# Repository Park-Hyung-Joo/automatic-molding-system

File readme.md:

--------------------------------------------
# Plastic Injection Molding Control System

## Abstract

This work was developed by the startup 'The Fourth Space', where senior Kim Seong-jun from the 17th generation of Barami is affiliated, as an outsourcing project for Barami's plastic injection molding machine control system.

The system is mainly divided into a heating bed (heater) that melts the plastic, a temperature sensor, and a solenoid valve that applies pressure to the melted plastic. Both the heater and the valve operate on 220VAC alternating current.

To control the 220VAC AC heater, a triac, a bidirectional switching device, was used. To control multiple triacs, each control signal is input to a 3-state buffer using a shift resistor, and the control signal is generated at the appropriate timing through a zero-detection circuit to turn the buffer on/off. This method allows for controlling the power of the AC heater. Additionally, the temperature of the AC heater is measured using a K-type temperature sensor, and by comparing it with the target temperature, the AC heater can be controlled within a range of 10 degrees of error through ON/OFF control. The solenoid valve also operates on 220VAC, so it is controlled in the same way using a triac.

--------------------------------------------------

## 220VAC Heater Control

### Triac

A triac is a bidirectional switching device for high voltage and high current. When a pulse signal is given to the Gate, it shorts between A1 and A2 as long as the voltage value is above a certain level, and it disconnects again when the voltage drops below a threshold. The direction doesn't matter. In other words, by providing a pulse when the instantaneous voltage of the AC is 0, AC current can flow through the triac. This can be used to control the current flowing to the heater and valve.

## Triac control system

### Optocoupler Circuit

When pulses are provided to tr1~tr6 at the appropriate timing, AC current flows to the heaters connected to J3, J4, and J5. When the pulse supply is stopped, the current is cut off from the moment the AC instantaneous voltage becomes 0. The MOC3021(U1U6) device is an optocoupler, which separates the high current, high voltage AC circuit from the low voltage, low current DC circuit.

### Pulse Generator

The circuit that generates the pulse produces a pulse at J3 the moment the AC voltage becomes 0. The detailed principle is as follows:

220VAC is rectified through bridge diodes and, through a resistor, provides the Photocoupler 4N35 with a rectified signal that has the same phase as 220VAC but at a lower voltage. When voltage is applied to the primary side of the 4N35, the secondary side's bjt operates, making the zero detection signal become 0. When the primary side voltage is 0, the bjt does not operate, and the zero detection voltage becomes VDC. Therefore, a pulse is generated the moment the voltage of 220VAC becomes 0.

This pulse is input into the 3-state buffer circuit.

### Tri-state Buffers

The tri-state buffer (buffer hereafter) circuit is divided into pulseIn, signal input, and pulseOut. When 0 is input to the signal input, the buffer passes the pulse, and when 1 is input, the pulse is blocked in the buffer. PulseOut is connected to tr1~tr6 of the above optocoupler circuit (there are a total of 3 optocoupler circuit boards). The triac is controlled by determining the signal value given to the buffer from the Arduino.

### Shift Registers

Directly inputting signals from the Arduino is unstable due to reasons like the insufficient number of Arduino pins and unstable signal current. Therefore, a method was chosen to store pre-determined signals in the shift register and connect the shift register output to the buffer signal end.

--------------------------------------------

## Temperature Measuring

To determine the current supplied to the heater, the temperature of the heating blocks must be measured. The temperature measurement circuit is composed of multiple temperature sensors and a decoder circuit to control them

### Temperature Sensers

The advantage of the K-type temperature sensor is its wide usable temperature range. It's suitable for systems that need to operate at high temperatures, which is why it was used in this project.

### Temperature Senser Connection Bus

The temperature sensor communicates its measurements to the Arduino via SPI communication. SCK is the clock, SO is the data, and CS is the pin that determines the communication blockage.

### Decoders

Since the Arduino can access only one temperature sensor at a time, only the selected temperature sensor should be connected to the Arduino, and the rest should be temporarily disconnected. The CS pin of the temperature sensor serves this function, and the values to be input into the CS pins are output through the decoder. The Arduino selects the temperature sensor to connect by inputting binary numbers to the decoder.

---------------------------------------------------------

## Solenoid Valve
<video src="./assets/img/valve.mp4" width="720px"></video>

A solenoid valve is applied to press the melted plastic. The control method is the same as the heater, using a triac. Since the same type of circuit is used, a detailed circuit description is omitted.

--------------------------------------------------------

## Raspberry Pi

While controlling the system with Arduino is sufficient, the client requested remote control functionality through a web application, so the Arduino was connected to the web via a Raspberry Pi.

--------------------------------------------------------

## Assembled Borads

This is how the circuit board looks when connected to the machine.

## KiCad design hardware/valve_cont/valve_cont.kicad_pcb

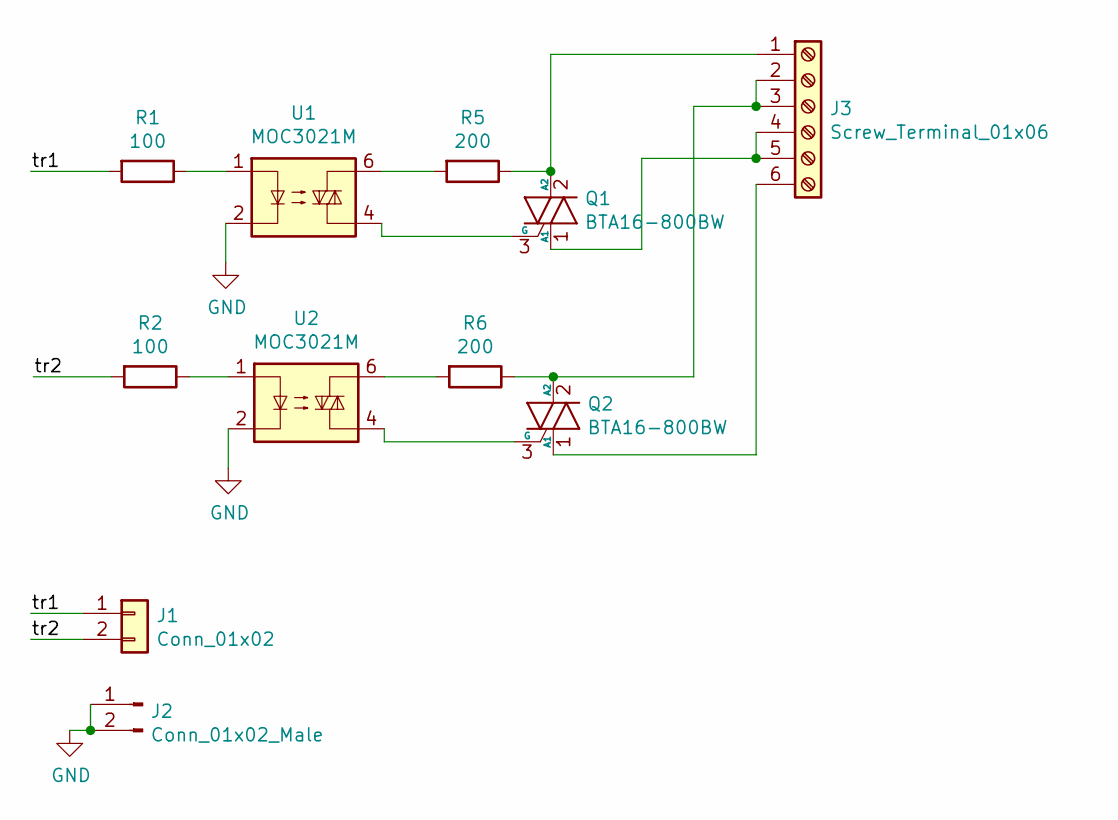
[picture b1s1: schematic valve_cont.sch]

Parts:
J1: Conn_01x02; Molex_SPOX_5267-02A_1x02_P2.50mm_Vertical
J2: Conn_01x02_Male; Molex_SPOX_5267-02A_1x02_P2.50mm_Vertical
J3: Screw_Terminal_01x06; BR_762K_6pin
Q1, Q2: BTA16-800BW; TO-220-3_Vertical
R1, R2: 100; R_Axial_DIN0207_L6.3mm_D2.5mm_P2.54mm_Vertical
R5, R6: 200; R_Axial_DIN0207_L6.3mm_D2.5mm_P2.54mm_Vertical
U1, U2: MOC3021M; DIP-6_W7.62mm_Socket

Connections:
/tr1: J1.1, R1.2
/tr2: J1.2, R2.2
GND: J2.1, J2.2, U1.2, U2.2
unnamed: J3.1, Q1.2 (A2), R5.1
unnamed: J3.2, J3.3, Q2.2 (A2), R6.1
unnamed: J3.4, J3.5, Q1.1 (A1)
unnamed: J3.6, Q2.1 (A1)
unnamed: Q1.3 (G), U1.4
unnamed: Q2.3 (G), U2.4
unnamed: R1.1, U1.1
unnamed: R2.1, U2.1
unnamed: R5.2, U1.6
unnamed: R6.2, U2.6

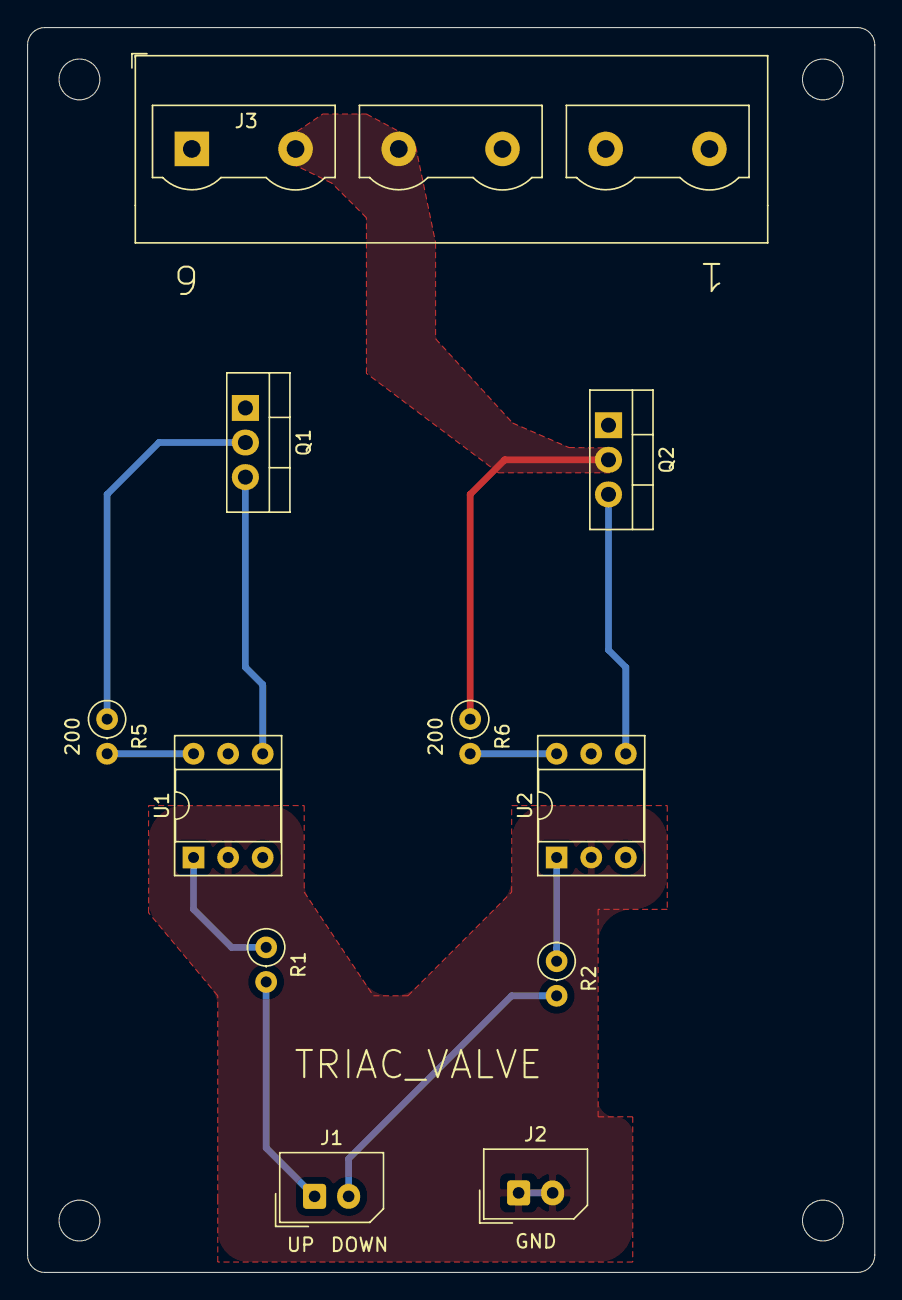
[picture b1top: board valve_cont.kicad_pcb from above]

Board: 2 copper layers, 62.2 x 91.4 mm, 11 parts (0 on the bottom side), 13 nets.

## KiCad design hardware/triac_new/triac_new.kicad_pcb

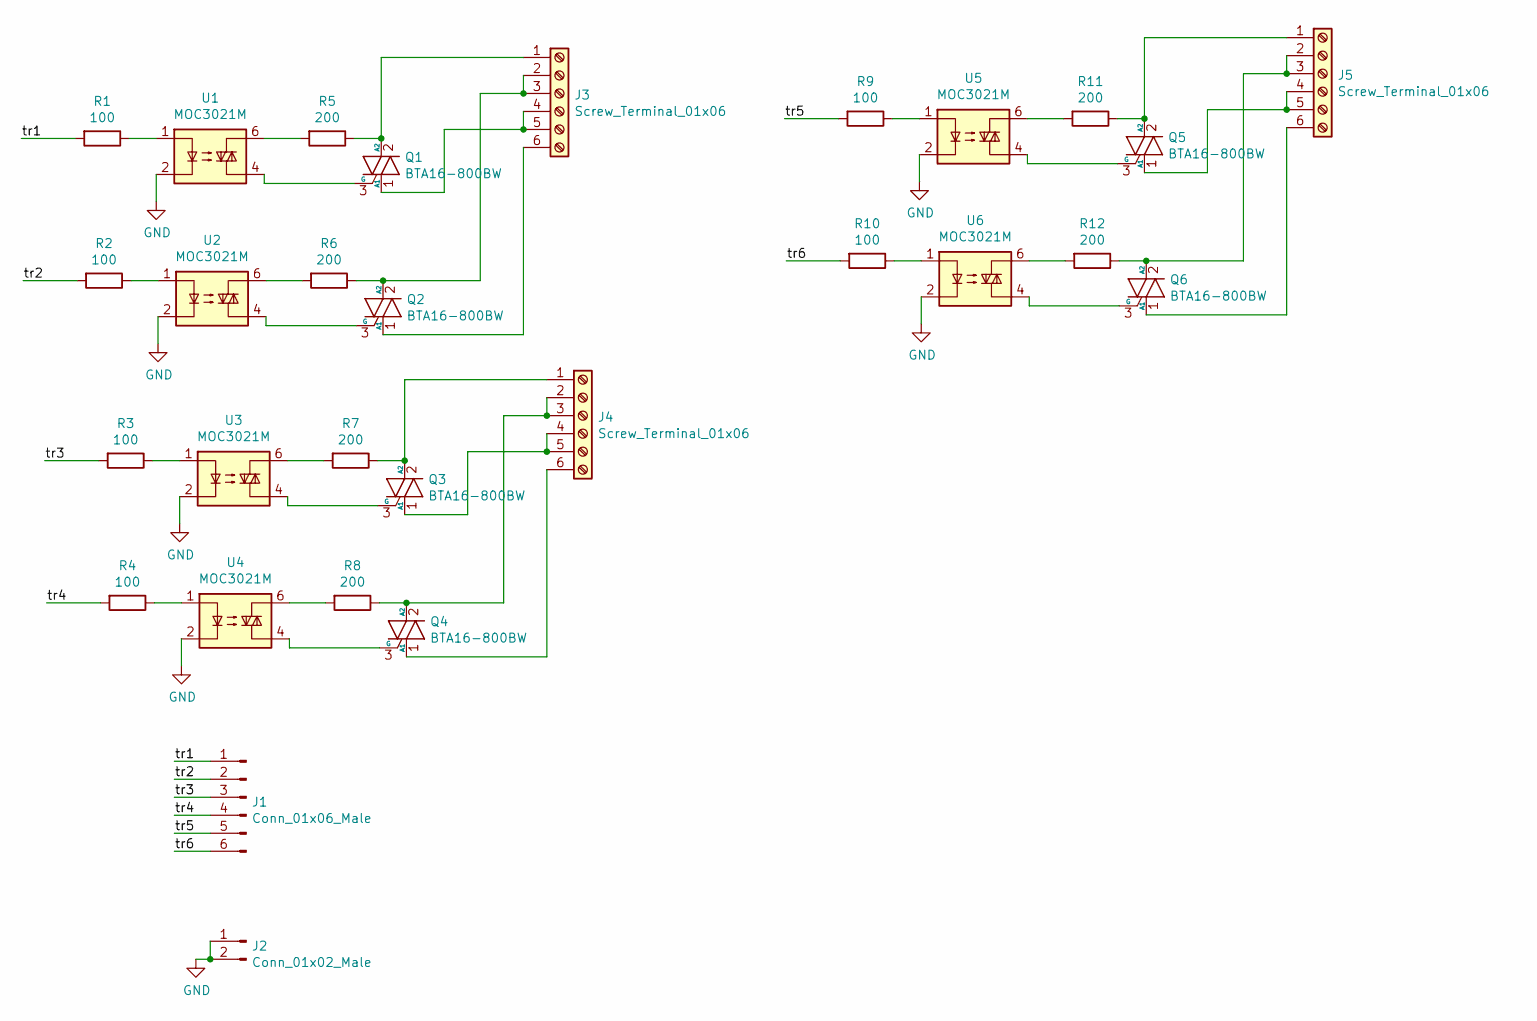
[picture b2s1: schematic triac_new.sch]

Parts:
J1: Conn_01x06_Male; Molex_SPOX_5267-06A_1x06_P2.50mm_Vertical
J2: Conn_01x02_Male; Molex_SPOX_5267-02A_1x02_P2.50mm_Vertical
J3, J4, J5: Screw_Terminal_01x06; BR_762K_6pin
Q1, Q2, Q3, Q4, Q5, Q6: BTA16-800BW; TO-220-3_Vertical
R1, R2, R3, R4, R9, R10: 100; R_Axial_DIN0207_L6.3mm_D2.5mm_P2.54mm_Vertical
R5, R6, R7, R8, R11, R12: 200; R_Axial_DIN0207_L6.3mm_D2.5mm_P2.54mm_Vertical
U1, U2, U3, U4, U5, U6: MOC3021M; DIP-6_W7.62mm_Socket

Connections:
/tr1: J1.1, R1.2
/tr2: J1.2, R2.2
/tr3: J1.3, R3.2
/tr4: J1.4, R4.2
/tr5: J1.5, R9.2
/tr6: J1.6, R10.2
GND: J2.1, J2.2, U1.2, U2.2, U3.2, U4.2, U5.2, U6.2
unnamed: J3.1, Q1.2 (A2), R5.1
unnamed: J3.2, J3.3, Q2.2 (A2), R6.1
unnamed: J3.4, J3.5, Q1.1 (A1)
unnamed: J3.6, Q2.1 (A1)
unnamed: J4.1, Q3.2 (A2), R7.1
unnamed: J4.2, J4.3, Q4.2 (A2), R8.1
unnamed: J4.4, J4.5, Q3.1 (A1)
unnamed: J4.6, Q4.1 (A1)
unnamed: J5.1, Q5.2 (A2), R11.1
unnamed: J5.2, J5.3, Q6.2 (A2), R12.1
unnamed: J5.4, J5.5, Q5.1 (A1)
unnamed: J5.6, Q6.1 (A1)
unnamed: Q1.3 (G), U1.4
unnamed: Q2.3 (G), U2.4
unnamed: Q3.3 (G), U3.4
unnamed: Q4.3 (G), U4.4
unnamed: Q5.3 (G), U5.4
unnamed: Q6.3 (G), U6.4
unnamed: R1.1, U1.1
unnamed: R2.1, U2.1
unnamed: R3.1, U3.1
unnamed: R4.1, U4.1
unnamed: R5.2, U1.6
unnamed: R6.2, U2.6
unnamed: R7.2, U3.6
unnamed: R8.2, U4.6
unnamed: R9.1, U5.1
unnamed: R10.1, U6.1
unnamed: R11.2, U5.6
unnamed: R12.2, U6.6

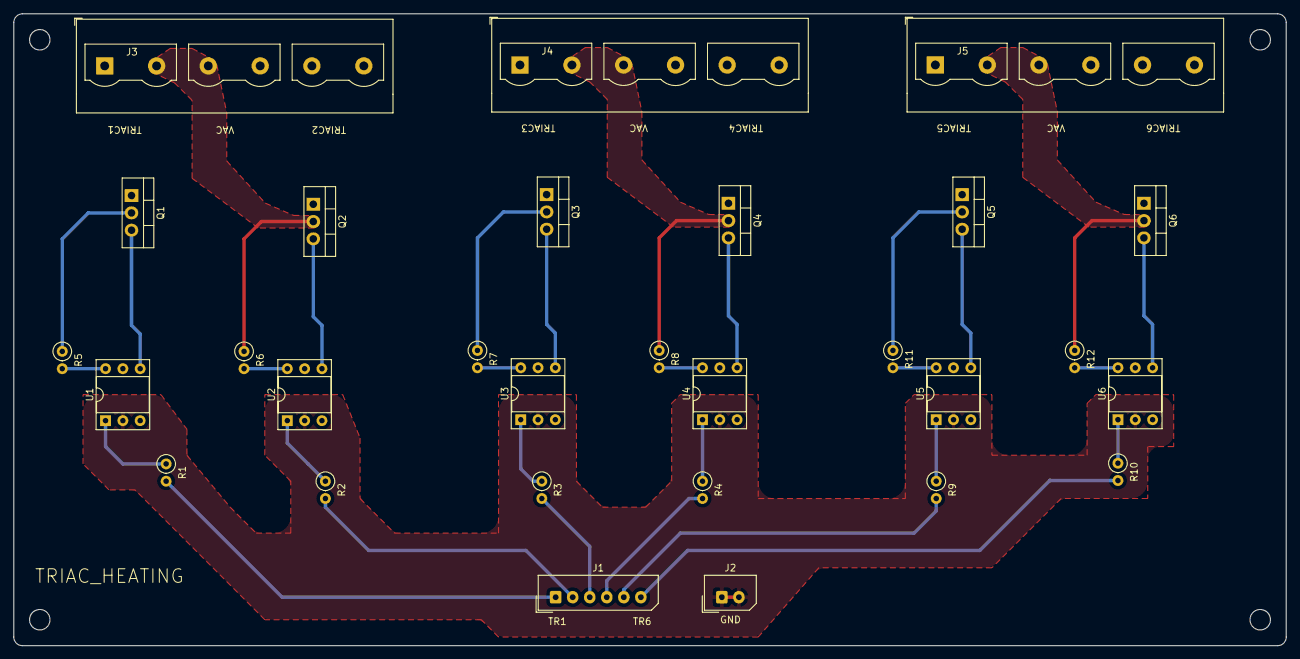
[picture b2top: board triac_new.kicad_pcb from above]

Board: 2 copper layers, 186.7 x 92.7 mm, 29 parts (0 on the bottom side), 37 nets.

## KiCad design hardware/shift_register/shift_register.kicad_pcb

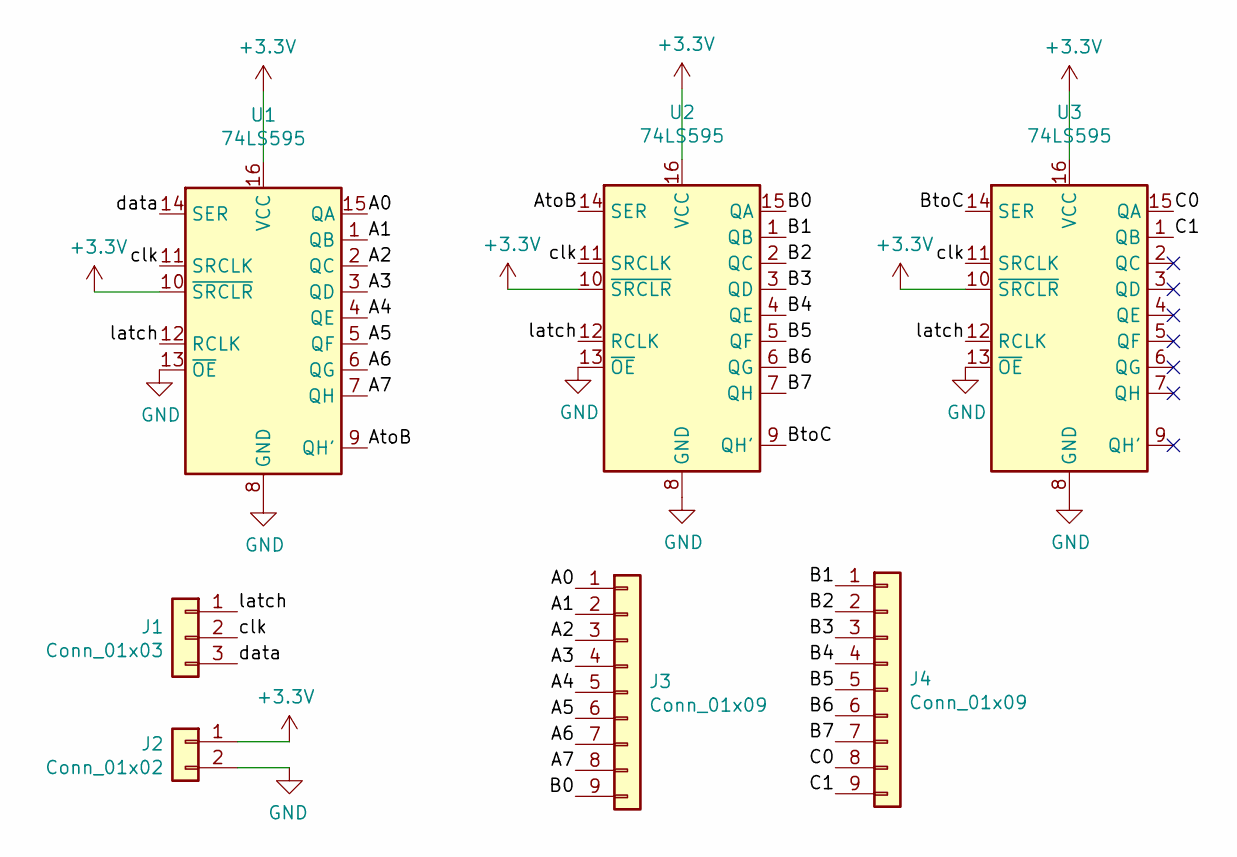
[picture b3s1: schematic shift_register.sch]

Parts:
J1: Conn_01x03; Molex_SPOX_5267-03A_1x03_P2.50mm_Vertical
J2: Conn_01x02; Molex_SPOX_5267-02A_1x02_P2.50mm_Vertical
J3, J4: Conn_01x09; Molex_SPOX_5267-09A_1x09_P2.50mm_Vertical
U1, U2, U3: 74LS595; DIP-16_W7.62mm_Socket

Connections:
+3V3: J2.1, U1.10 (~SRCLR), U1.16 (VCC), U2.10 (~SRCLR), U2.16 (VCC), U3.10 (~SRCLR), U3.16 (VCC)
/A0: J3.1, U1.15 (QA)
/A1: J3.2, U1.1 (QB)
/A2: J3.3, U1.2 (QC)
/A3: J3.4, U1.3 (QD)
/A4: J3.5, U1.4 (QE)
/A5: J3.6, U1.5 (QF)
/A6: J3.7, U1.6 (QG)
/A7: J3.8, U1.7 (QH)
/AtoB: U1.9 (QH'), U2.14 (SER)
/B0: J3.9, U2.15 (QA)
/B1: J4.1, U2.1 (QB)
/B2: J4.2, U2.2 (QC)
/B3: J4.3, U2.3 (QD)
/B4: J4.4, U2.4 (QE)
/B5: J4.5, U2.5 (QF)
/B6: J4.6, U2.6 (QG)
/B7: J4.7, U2.7 (QH)
/BtoC: U2.9 (QH'), U3.14 (SER)
/C0: J4.8, U3.15 (QA)
/C1: J4.9, U3.1 (QB)
/clk: J1.2, U1.11 (SRCLK), U2.11 (SRCLK), U3.11 (SRCLK)
/data: J1.3, U1.14 (SER)
/latch: J1.1, U1.12 (RCLK), U2.12 (RCLK), U3.12 (RCLK)
GND: J2.2, U1.8 (GND), U1.13 (~OE), U2.8 (GND), U2.13 (~OE), U3.8 (GND), U3.13 (~OE)

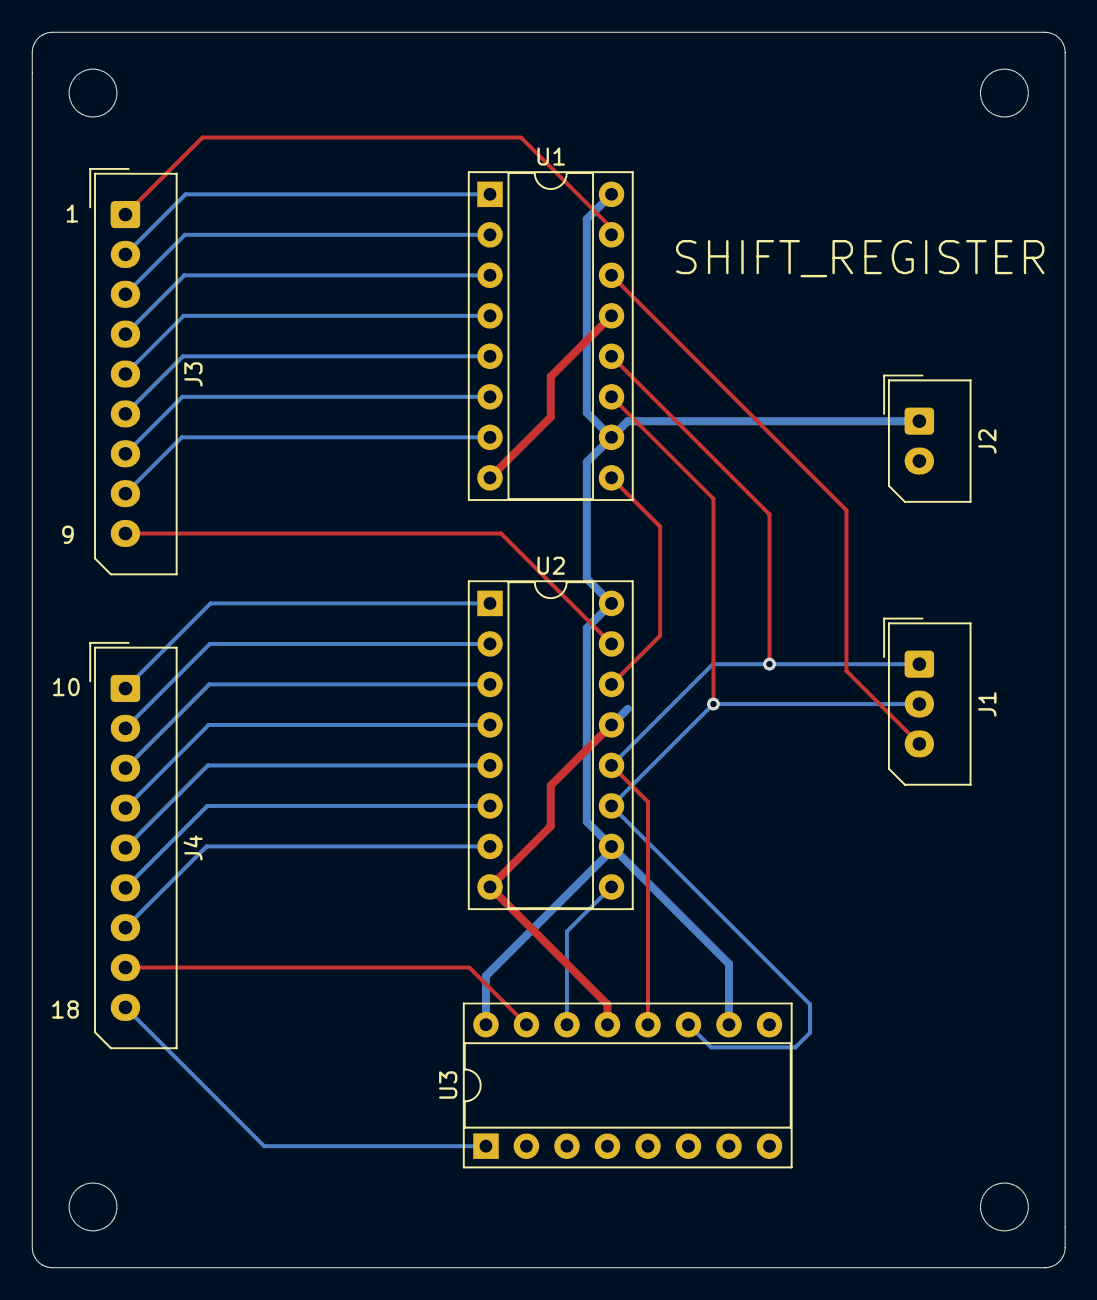
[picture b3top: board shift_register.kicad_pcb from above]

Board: 2 copper layers, 64.8 x 77.5 mm, 7 parts (0 on the bottom side), 25 nets.

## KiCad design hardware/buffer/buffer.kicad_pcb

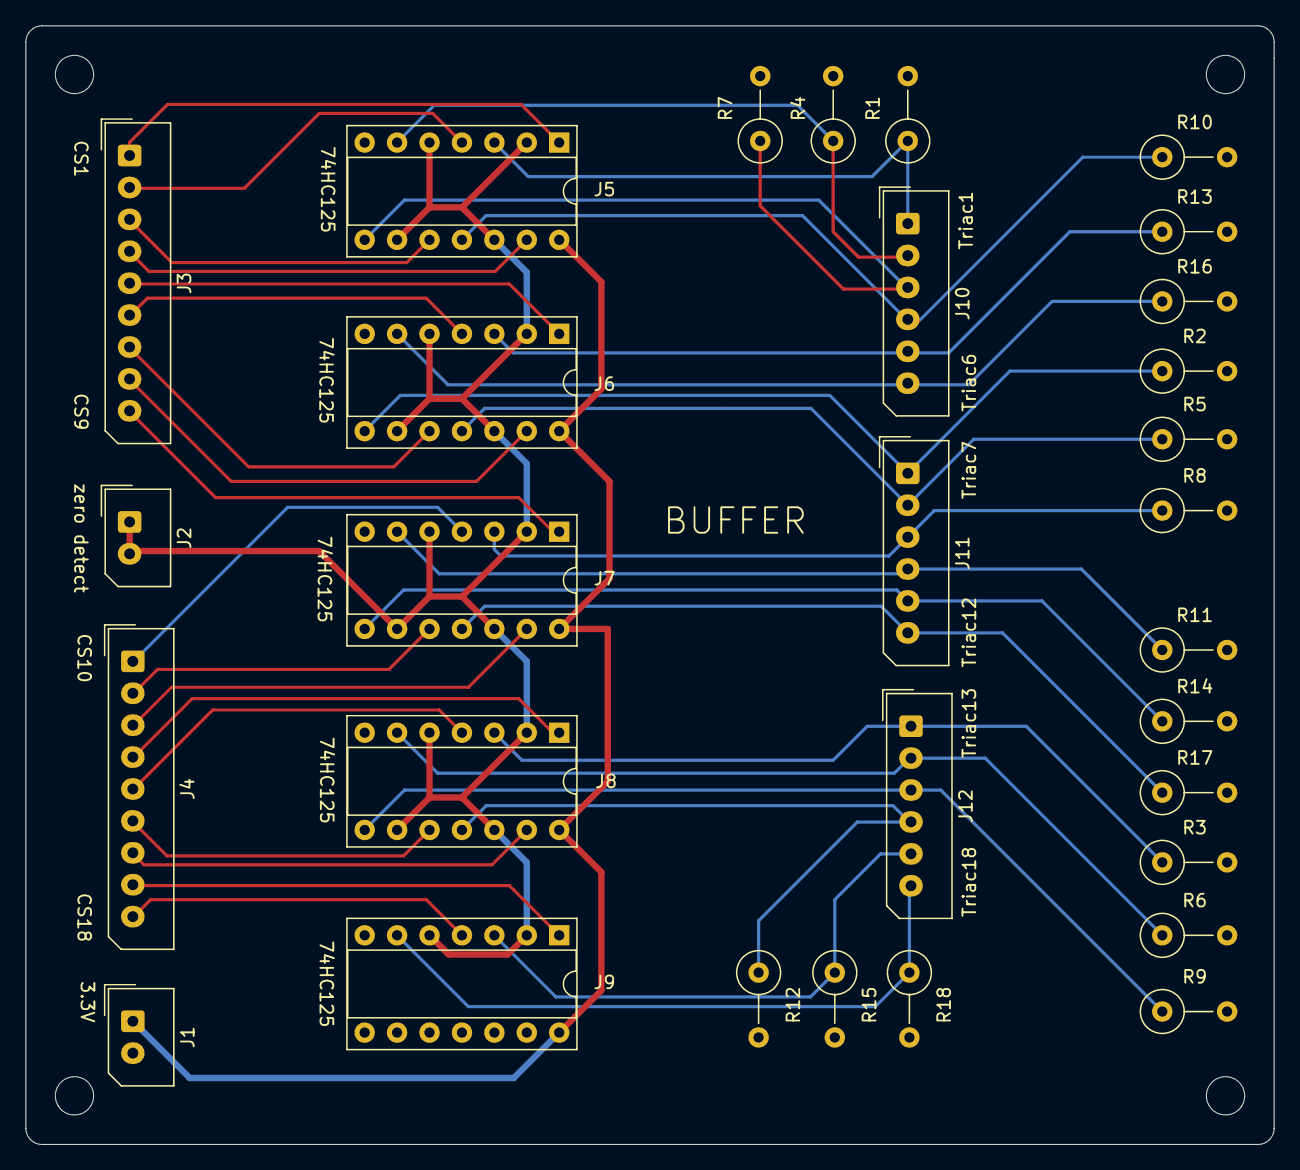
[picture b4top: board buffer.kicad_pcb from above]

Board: 2 copper layers, 97.8 x 87.6 mm, 30 parts (0 on the bottom side), 39 nets.

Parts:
J1, J2: Conn_01x02; Molex_SPOX_5267-02A_1x02_P2.50mm_Vertical
J3, J4: Conn_01x09; Molex_SPOX_5267-09A_1x09_P2.50mm_Vertical
J5, J6, J7, J8, J9: Conn_02x07_Counter_Clockwise; DIP-14_W7.62mm_Socket
J10, J11, J12: Conn_01x06; Molex_SPOX_5267-06A_1x06_P2.50mm_Vertical
R1, R2, R3, R4, R5, R6, R7, R8, R9, R10, R11, R12, R13, R14, R15, R16, R17, R18: R; R_Axial_DIN0309_L9.0mm_D3.2mm_P5.08mm_Vertical

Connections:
+3V3: J1.1, J5.14, J6.14, J7.14, J8.14, J9.14
/C1: J3.1, J5.1
/C2: J3.2, J5.4
/C3: J3.3, J5.10
/C4: J3.4, J5.13
/C5: J3.5, J6.1
/C6: J3.6, J6.4
/C7: J3.7, J6.10
/C8: J3.8, J6.13
/C9: J3.9, J7.1
/C10: J4.1, J7.4
/C11: J4.2, J7.10
/C12: J4.3, J7.13
/C13: J4.4, J8.1
/C14: J4.5, J8.4
/C15: J4.6, J8.10
/C16: J4.7, J8.13
/C17: J4.8, J9.1
/C18: J4.9, J9.4
/Tri1: J5.3, J10.1, R1.1
/Tri2: J5.6, J10.2, R4.1
/Tri3: J5.8, J10.3, R7.1
/Tri4: J5.11, J10.4, R10.1
/Tri5: J6.3, J10.5, R13.1
/Tri6: J6.6, J10.6, R16.1
/Tri7: J6.8, J11.1, R2.1
/Tri8: J6.11, J11.2, R5.1
/Tri9: J7.3, J11.3, R8.1
/Tri10: J7.6, J11.4, R11.1
/Tri11: J7.8, J11.5, R14.1
/Tri12: J7.11, J11.6, R17.1
/Tri13: J8.3, J12.1, R3.1
/Tri14: J8.6, J12.2, R6.1
/Tri15: J8.8, J12.3, R9.1
/Tri16: J8.11, J12.4, R12.1
/Tri17: J9.3, J12.5, R15.1
/Tri18: J9.6, J12.6, R18.1
/pulse: J2.1, J2.2, J5.2, J5.5, J5.9, J5.12, J6.2, J6.5, J6.9, J6.12, J7.2, J7.5, J7.9, J7.12, J8.2, J8.5, J8.9, J8.12, J9.2, J9.5
GND: J1.2, J5.7, J6.7, J7.7, J8.7, J9.7, R1.2, R2.2, R3.2, R4.2, R5.2, R6.2, R7.2, R8.2, R9.2, R10.2, R11.2, R12.2, R13.2, R14.2, R15.2, R16.2, R17.2, R18.2

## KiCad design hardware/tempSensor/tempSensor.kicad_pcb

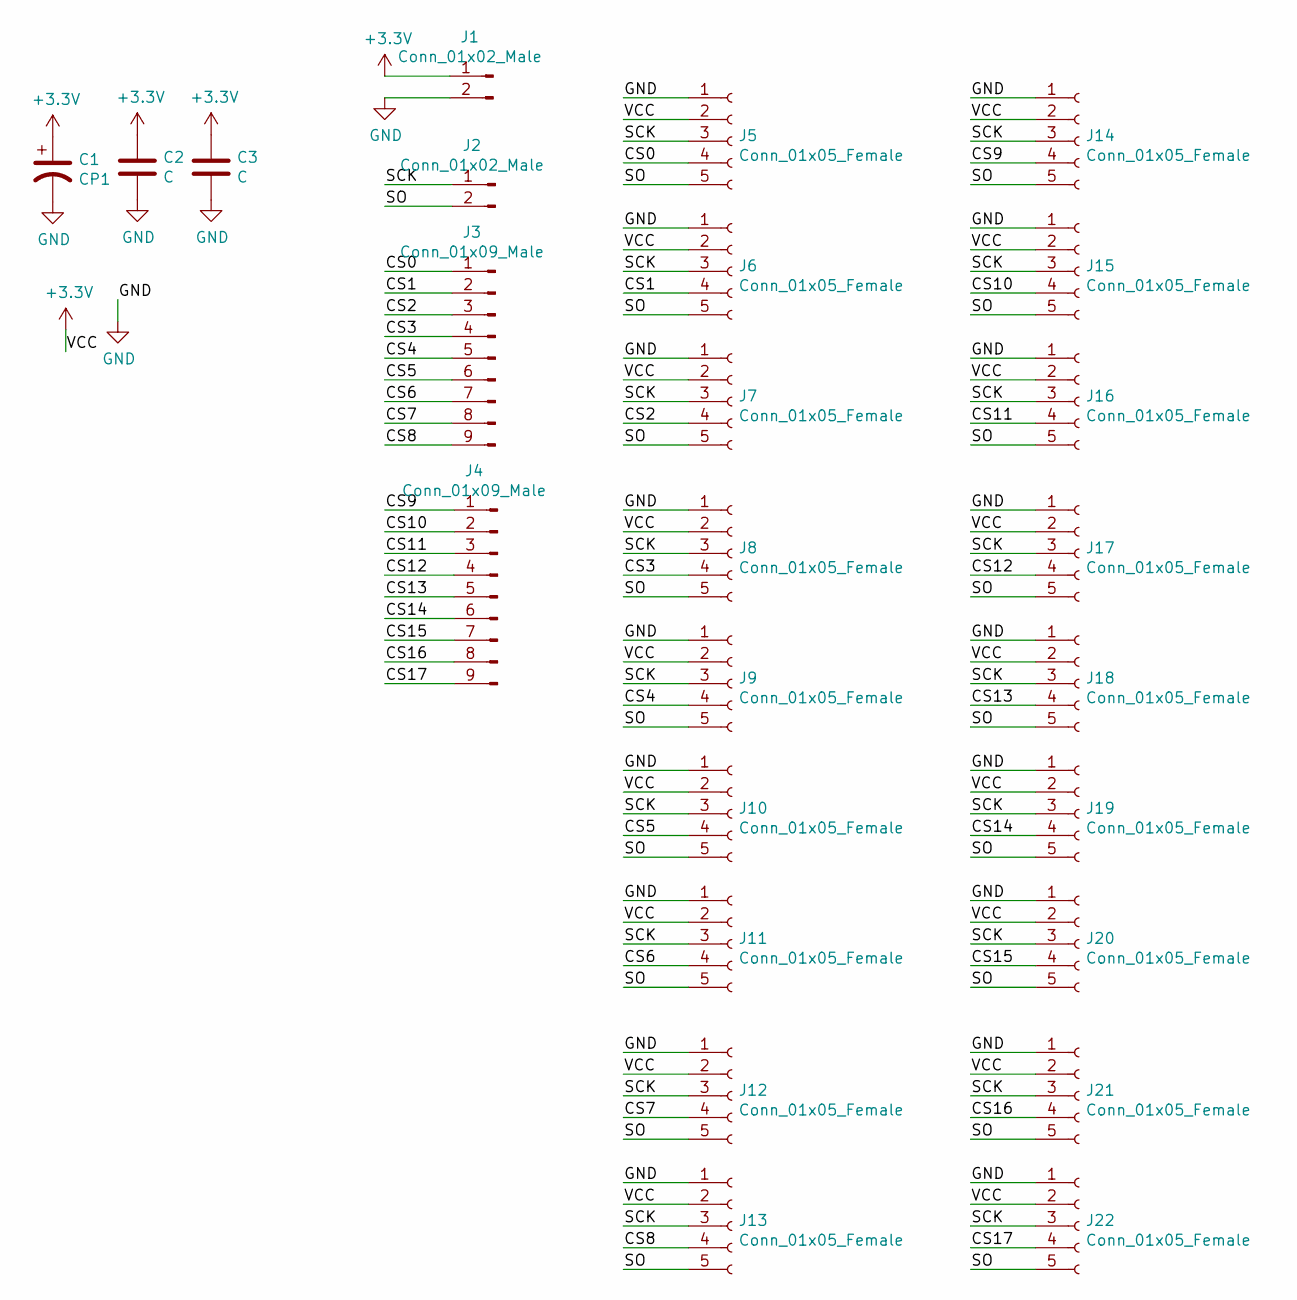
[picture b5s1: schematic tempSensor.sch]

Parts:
C1: CP1; CP_Radial_D8.0mm_P5.00mm
C2, C3: C; C_Axial_L3.8mm_D2.6mm_P7.50mm_Horizontal
J1, J2: Conn_01x02_Male; Molex_SPOX_5267-02A_1x02_P2.50mm_Vertical
J3, J4: Conn_01x09_Male; Molex_SPOX_5267-09A_1x09_P2.50mm_Vertical
J5, J6, J7, J8, J9, J10, J11, J12, J13, J14, J15, J16, J17, J18, J19, J20, J21, J22: Conn_01x05_Female; PinSocket_1x05_P2.54mm_Vertical

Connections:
+3V3: C1.1, C2.1, C3.1, J1.1, J5.2, J6.2, J7.2, J8.2, J9.2, J10.2, J11.2, J12.2, J13.2, J14.2, J15.2, J16.2, J17.2, J18.2, J19.2, J20.2, J21.2, J22.2
/CS0: J3.1, J5.4
/CS1: J3.2, J6.4
/CS2: J3.3, J7.4
/CS3: J3.4, J8.4
/CS4: J3.5, J9.4
/CS5: J3.6, J10.4
/CS6: J3.7, J11.4
/CS7: J3.8, J12.4
/CS8: J3.9, J13.4
/CS9: J4.1, J14.4
/CS10: J4.2, J15.4
/CS11: J4.3, J16.4
/CS12: J4.4, J17.4
/CS13: J4.5, J18.4
/CS14: J4.6, J19.4
/CS15: J4.7, J20.4
/CS16: J4.8, J21.4
/CS17: J4.9, J22.4
/SCK: J2.1, J5.3, J6.3, J7.3, J8.3, J9.3, J10.3, J11.3, J12.3, J13.3, J14.3, J15.3, J16.3, J17.3, J18.3, J19.3, J20.3, J21.3, J22.3
/SO: J2.2, J5.5, J6.5, J7.5, J8.5, J9.5, J10.5, J11.5, J12.5, J13.5, J14.5, J15.5, J16.5, J17.5, J18.5, J19.5, J20.5, J21.5, J22.5
GND: C1.2, C2.2, C3.2, J1.2, J5.1, J6.1, J7.1, J8.1, J9.1, J10.1, J11.1, J12.1, J13.1, J14.1, J15.1, J16.1, J17.1, J18.1, J19.1, J20.1, J21.1, J22.1

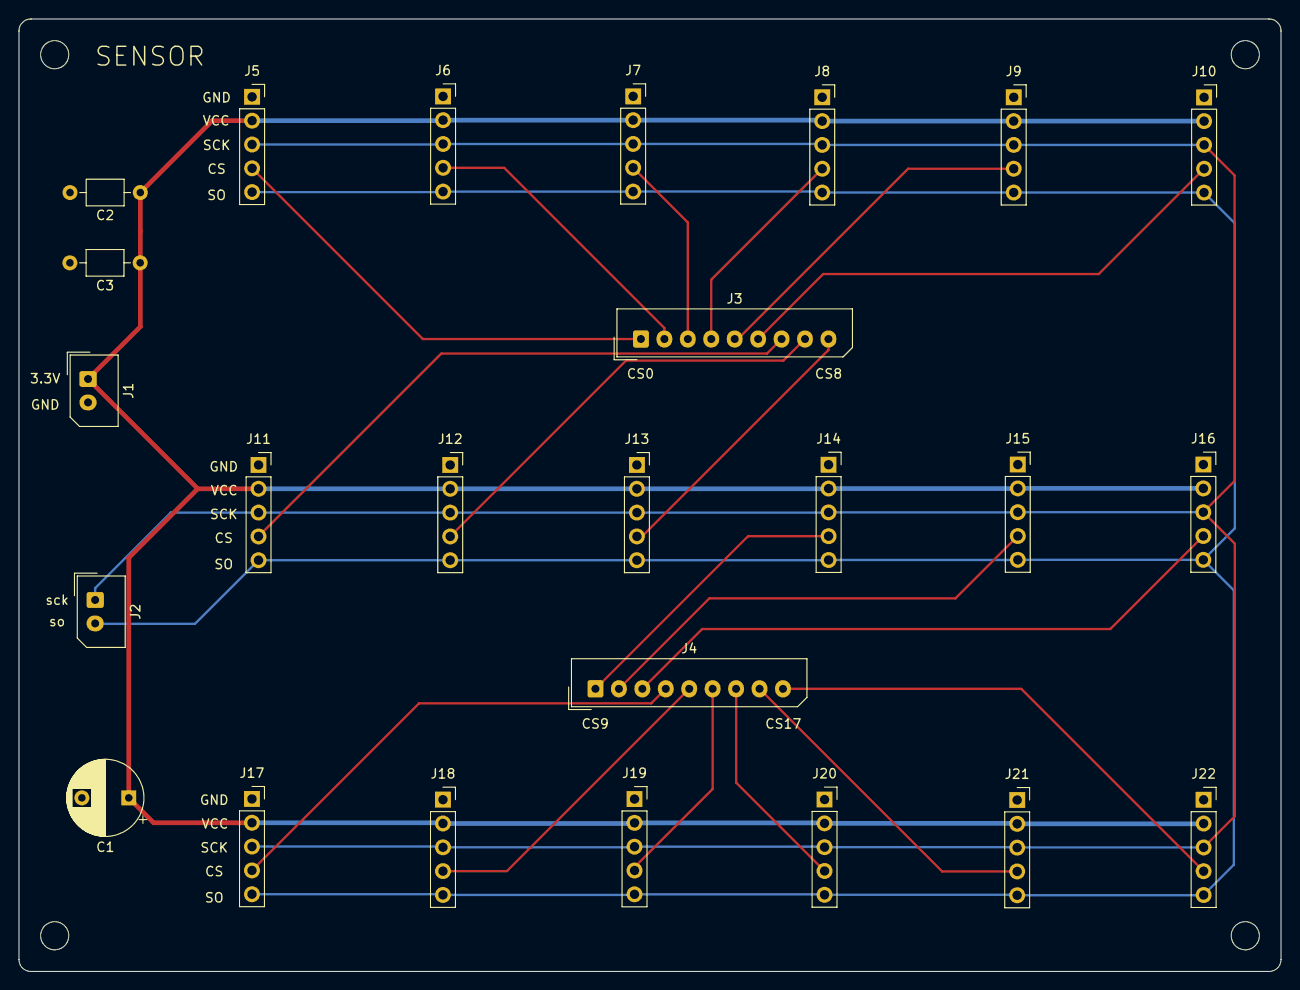
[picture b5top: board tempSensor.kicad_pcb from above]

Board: 2 copper layers, 134.6 x 101.6 mm, 25 parts (0 on the bottom side), 22 nets.

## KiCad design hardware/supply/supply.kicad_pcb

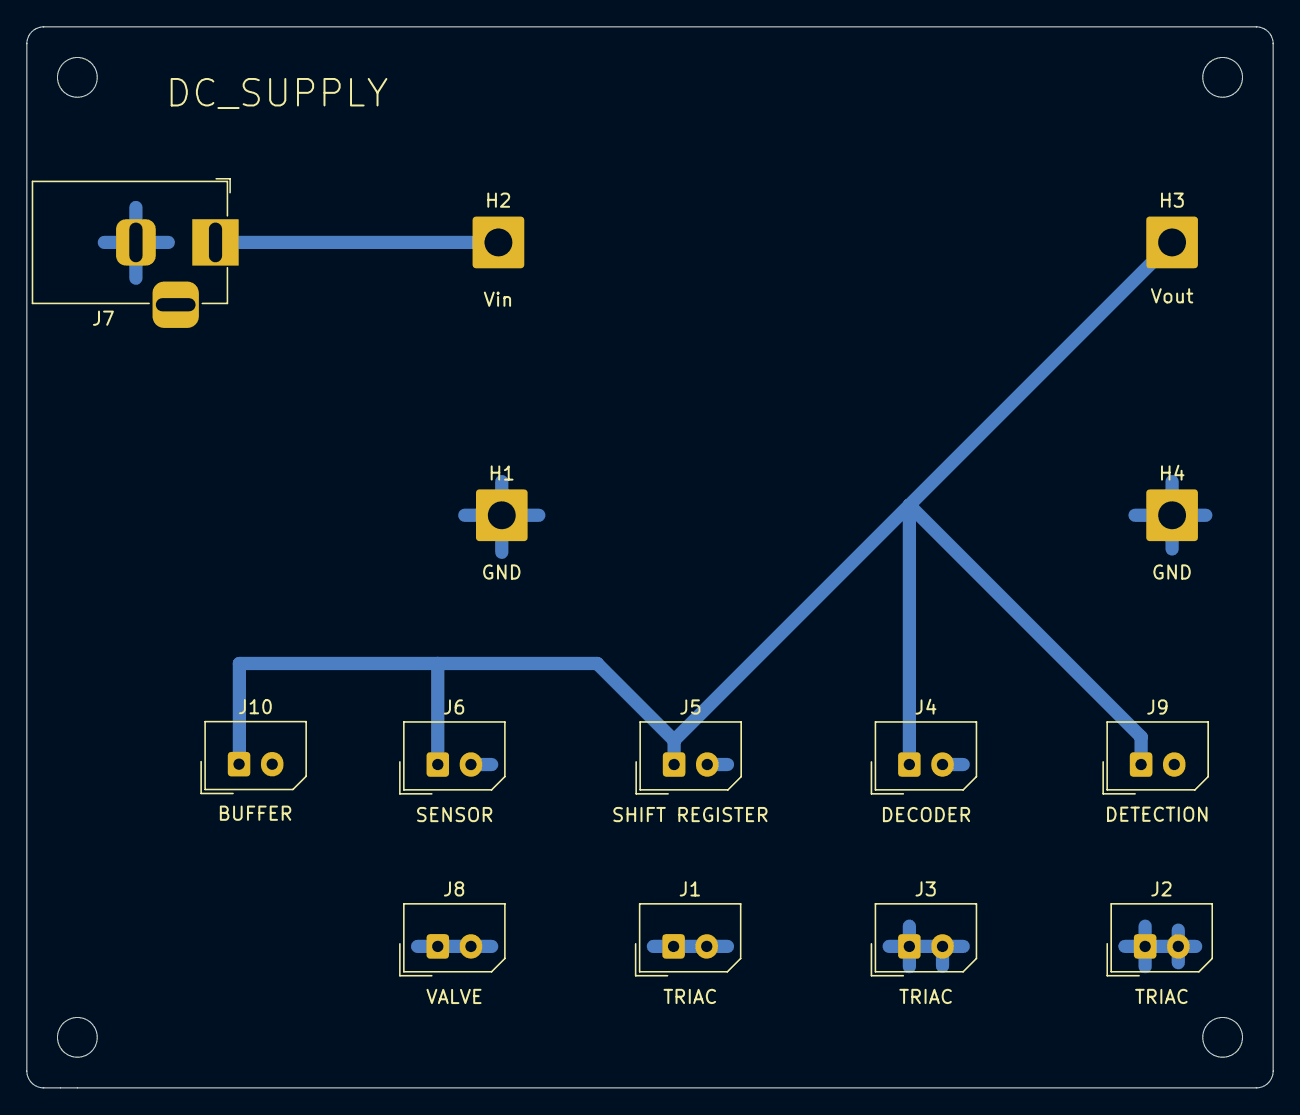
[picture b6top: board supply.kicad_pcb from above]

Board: 2 copper layers, 94.0 x 80.0 mm, 14 parts (0 on the bottom side), 3 nets.

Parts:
H1, H2, H3, H4: MountingHole_Pad; SolderWire-1.5sqmm_1x01_D1.7mm_OD3.9mm
J1, J2, J3, J4, J5, J6, J8, J9, J10: Conn_01x02_Male; Molex_SPOX_5267-02A_1x02_P2.50mm_Vertical
J7: Barrel_Jack_Switch; BarrelJack_Horizontal

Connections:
+3V3: H3.1, J4.1, J5.1, J6.1, J9.1, J10.1
+12V: H2.1, J7.1
GND: H1.1, H4.1, J1.1, J1.2, J2.1, J2.2, J3.1, J3.2, J4.2, J5.2, J6.2, J7.2, J8.1, J8.2, J9.2, J10.2

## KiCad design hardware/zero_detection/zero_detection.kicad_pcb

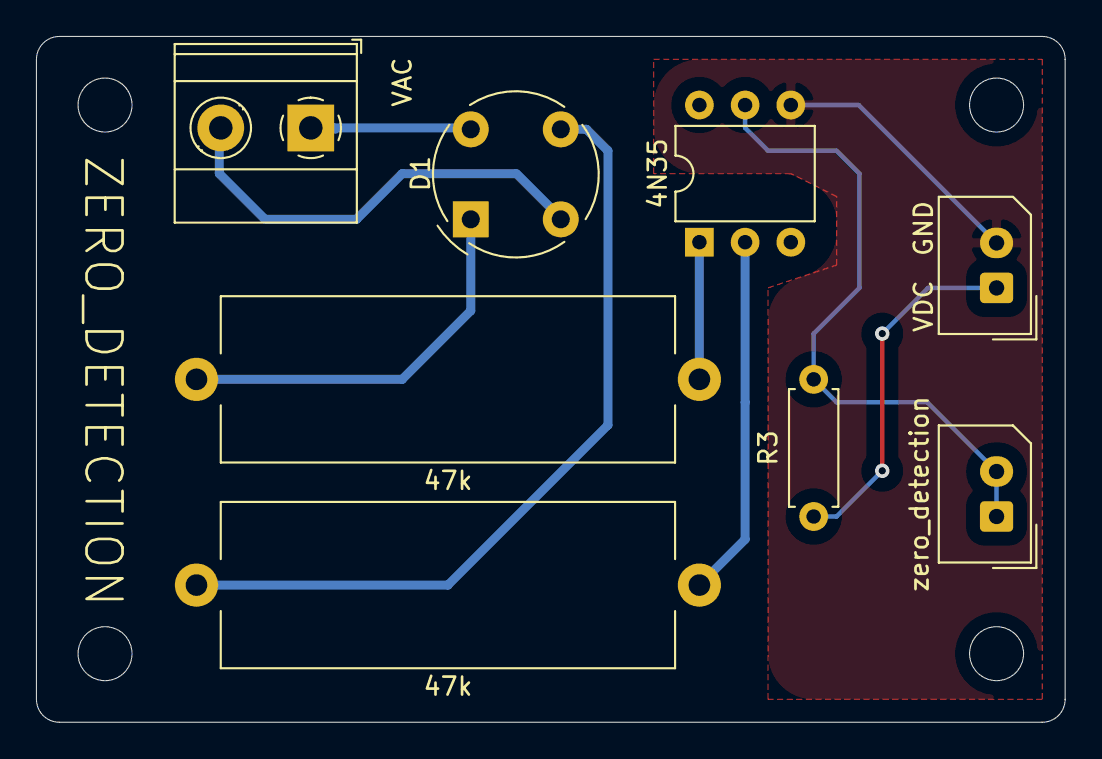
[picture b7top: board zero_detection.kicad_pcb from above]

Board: 2 copper layers, 57.2 x 38.1 mm, 8 parts (0 on the bottom side), 9 nets.

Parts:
4N35: 4N35; DIP-6_W7.62mm
47k, 47k#2: 47k; R_Axial_Power_L25.0mm_W9.0mm_P27.94mm
D1: D_Bridge_+A-A; Diode_Bridge_Round_D9.0mm
R3: 1k; R_Axial_DIN0207_L6.3mm_D2.5mm_P7.62mm_Horizontal
VAC: VAC; TerminalBlock_Phoenix_MKDS-1,5-2_1x02_P5.00mm_Horizontal
VDC: VDC; Molex_SPOX_5267-02A_1x02_P2.50mm_Vertical
zero_detection: zero_detection; Molex_SPOX_5267-02A_1x02_P2.50mm_Vertical

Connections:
GNDS: 4N35.4, VDC.2
unnamed: 47k#2.2, D1.1
unnamed: D1.2, VAC.2
unnamed: 47k.2, D1.3
unnamed: D1.4, VAC.1
unnamed: R3.1, VDC.1
unnamed: 4N35.5, R3.2, zero_detection.1, zero_detection.2
unnamed: 4N35.1, 47k#2.1
unnamed: 4N35.2, 47k.1

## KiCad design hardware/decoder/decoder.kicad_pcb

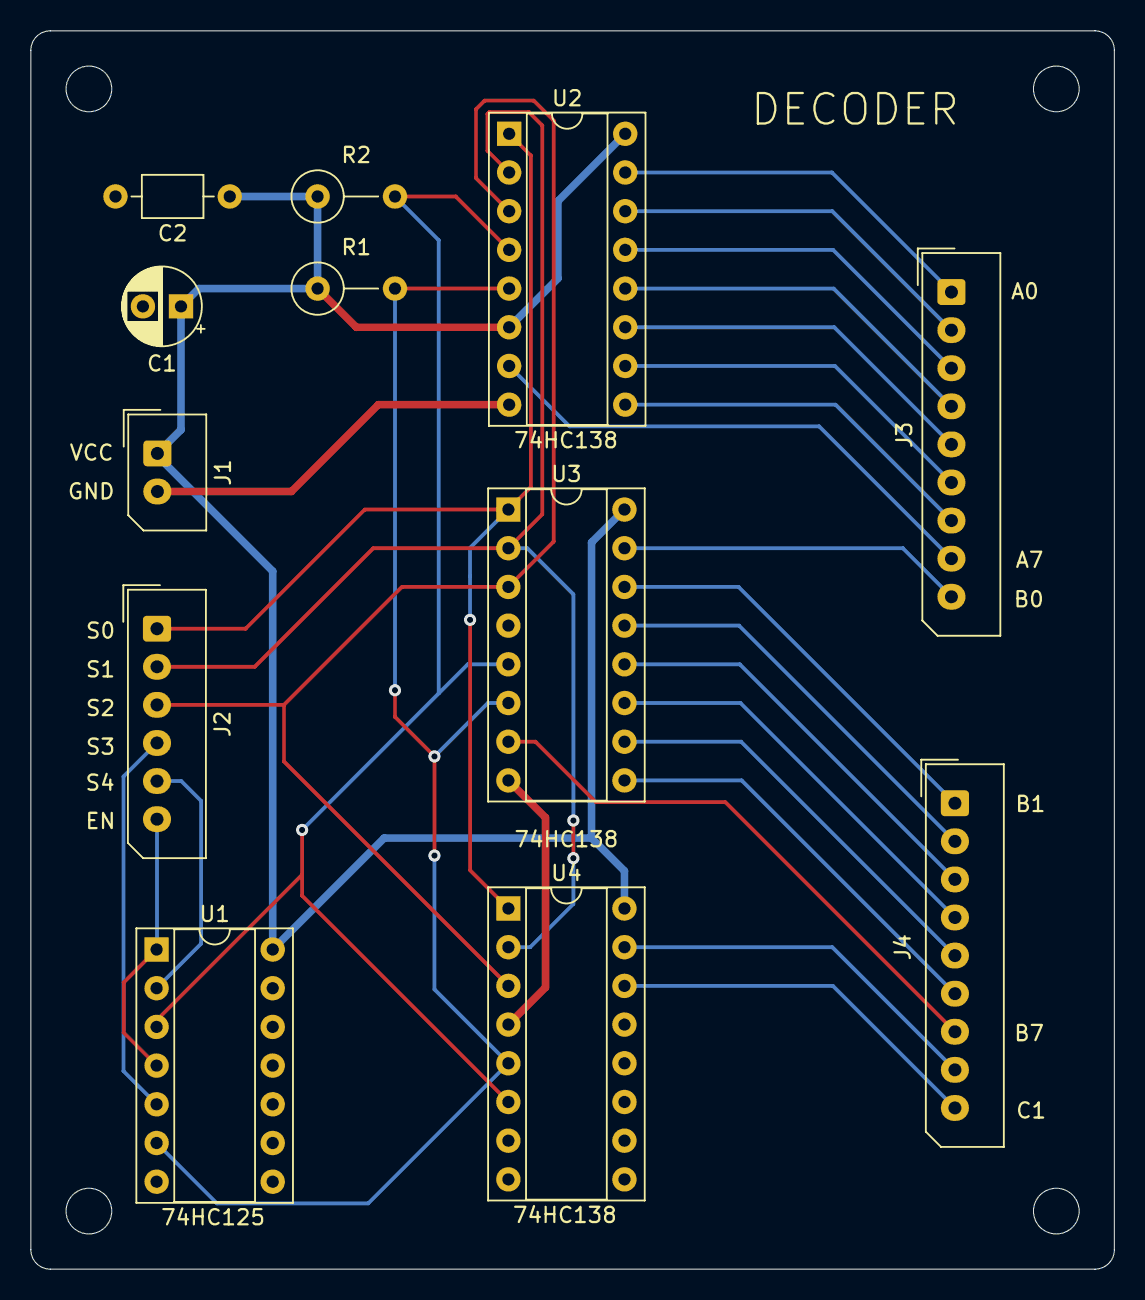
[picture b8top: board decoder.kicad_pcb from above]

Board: 2 copper layers, 71.1 x 81.3 mm, 12 parts (0 on the bottom side), 28 nets.

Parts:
C1: C; CP_Radial_D5.0mm_P2.50mm
C2: C; C_Axial_L3.8mm_D2.6mm_P7.50mm_Horizontal
J1: Conn_01x02; Molex_SPOX_5267-02A_1x02_P2.50mm_Vertical
J2: Conn_01x06; Molex_SPOX_5267-06A_1x06_P2.50mm_Vertical
J3, J4: Conn_01x09_Male; Molex_SPOX_5267-09A_1x09_P2.50mm_Vertical
R1, R2: R; R_Axial_DIN0309_L9.0mm_D3.2mm_P5.08mm_Vertical
U1: 74LS125; DIP-14_W7.62mm_Socket
U2, U3, U4: 74LS138; DIP-16_W7.62mm_Socket

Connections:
+3V3: C1.1, C2.1, J1.1, R1.1, R2.1, U1.14, U2.6, U2.16, U3.16, U4.16
/S3_out: R1.2, U1.6, U2.5, U3.6, U4.5
/S4_out: R2.2, U1.3, U2.4, U3.5, U4.6
A0: J3.1, U2.15
A1: J3.2, U2.14
A2: J3.3, U2.13
A3: J3.4, U2.12
A4: J3.5, U2.11
A5: J3.6, U2.10
A6: J3.7, U2.9
A7: J3.8, U2.7
B0: J3.9, U3.15
B1: J4.1, U3.14
B2: J4.2, U3.13
B3: J4.3, U3.12
B4: J4.4, U3.11
B5: J4.5, U3.10
B6: J4.6, U3.9
B7: J4.7, U3.7
C0: J4.8, U4.15
C1: J4.9, U4.14
GND: C1.2, C2.2, J1.2, U1.7, U2.8, U3.4, U3.8, U4.4, U4.8
ON: J2.6, U1.1, U1.4
S0: J2.1, U2.1, U3.1, U4.1
S1: J2.2, U2.2, U3.2, U4.2
S2: J2.3, U2.3, U3.3, U4.3
S3: J2.4, U1.5
S4: J2.5, U1.2

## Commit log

2023-08-23 ADD Readme FIX: access
